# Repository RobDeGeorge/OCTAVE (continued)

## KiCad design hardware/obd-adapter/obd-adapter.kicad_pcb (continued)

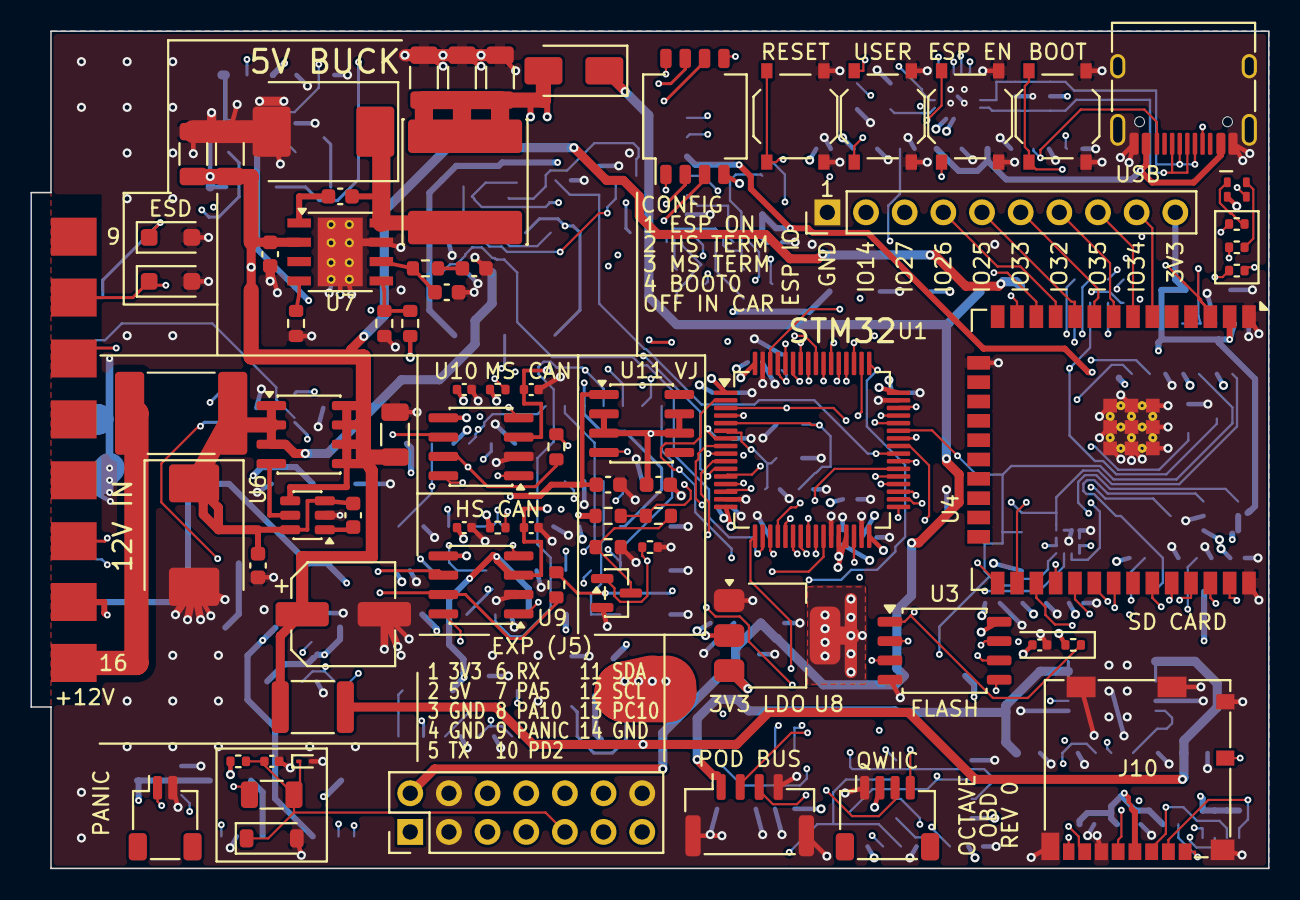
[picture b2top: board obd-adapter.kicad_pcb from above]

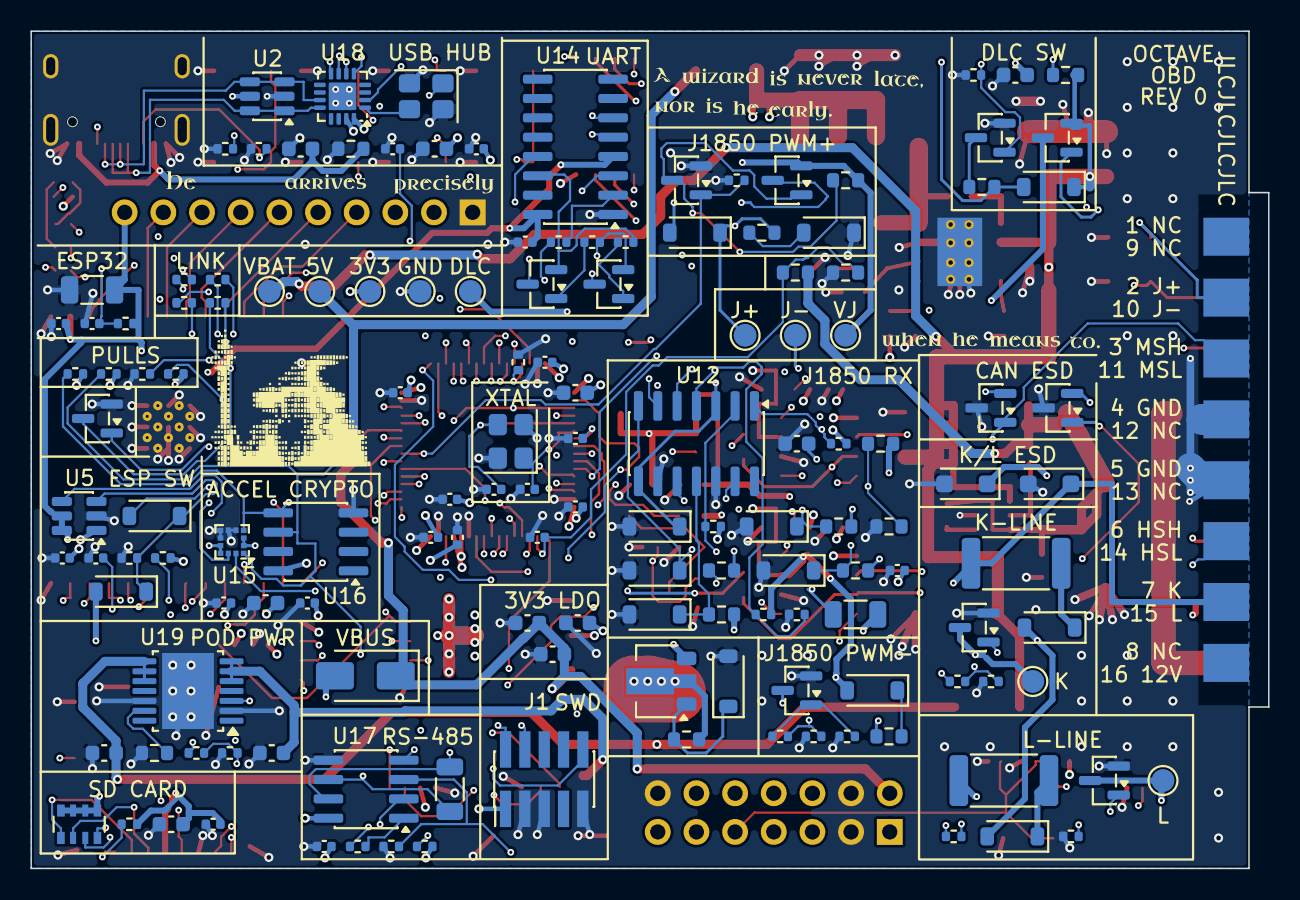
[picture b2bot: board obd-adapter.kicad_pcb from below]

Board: 6 copper layers, 81.3 x 55.0 mm, 218 parts (144 on the bottom side), 151 nets.

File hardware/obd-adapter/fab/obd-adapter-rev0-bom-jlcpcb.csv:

Comment,Designator,Footprint,LCSC
100n,"C1,C2,C3,C4,C6,C9,C13,C15,C35,C36,C37,C38,C39,C45,C46,C48,C49,C51,C54,C57,C58",C_0402_1005Metric,C307331
4.7u,C5,C_0603_1608Metric,C19666
1u,"C7,C16,C18,C56",C_0402_1005Metric,C52923
10p,"C10,C11",C_0402_1005Metric,C32949
10u,"C12,C32,C33,C34,C47,C50,C55",C_0603_1608Metric,C96446
22u,C14,C_1206_3216Metric,C12891
1n,C17,C_0402_1005Metric,C1523
100n,"C19,C20,C23,C26,C41,C43",C_0603_1608Metric,C14663
10u,C21,C_1206_3216Metric,C13585
47u 50V,C22,CP_Elec_6.3x7.7,C2887275
2.2u,"C24,C25",C_1206_3216Metric,C50254
6.8n,C27,C_0603_1608Metric,C1631
47p,C28,C_0603_1608Metric,C1671
47u,"C29,C30,C31",C_1206_3216Metric,C96123
1u,"C40,C42,C52,C53",C_0603_1608Metric,C15849
RGB,D1,LED_RGB_1615,C965840
5.0SMDJ33CA,D4,D_SMC,C2913642
B560C,D5,D_SMC,C85100
SS34,"D6,D7",D_SMA,C8678
SZNUP2105L,"D8,D9",SOT-23,C233494
BZT52C12,D10,D_SOD-123,C19077410
B5819W,"D11,D12,D13",D_SOD-123,C8598
BZT52C33,D14,D_SOD-123,C173417
1N4148W,"D15,D16,D17,D18,D21,D23,D26,D27",D_SOD-123,C81598
SMF24A,"D19,D20,D22,D24",D_SOD-123F,C19077514
ESD9B3.3ST5G,D28,D_SOD-923,C96512
BZT52C5V1,D30,D_SOD-123,C19077401
BZT52C30,D31,D_SOD-123,C19077418
2A 60V,F1,Fuse_2920_7451Metric,C49326266
0.5A 60V,F2,Fuse_1812_4532Metric,C19078719
SWD,J1,PinHeader_2x05_P1.27mm_Vertical_SMD,C41376037
USB-C,J2,USB_C_Receptacle_HRO_TYPE-C-31-M-12,C165948
Qwiic,J4,JST_SH_SM04B-SRSS-TB_1x04-1MP_P1.00mm_Horizontal,C160404
PANIC,J9,JST_SH_SM02B-SRSS-TB_1x02-1MP_P1.00mm_Horizontal,C160402
microSD,J10,microSD_HC_Molex_104031-0811,C585350
POD BUS,J11,JST_GH_SM04B-GHS-TB_1x04-1MP_P1.25mm_Horizontal,C189895
8.2u,L1,L_Changjiang_FNR8065S,C96978
AO4264E,Q1,SOIC-8_3.9x4.9mm_P1.27mm,C334232
SI2309CDS,Q2,SOT-23,C10493
AO3401A,Q6,SOT-23,C15127
MMBT3904,"Q7,Q8,Q9,Q10,Q11",SOT-23,C20526
2N7002,"Q3,Q4,Q5,Q14",SOT-23,C8545
BCX56-16,Q15,SOT-89-3,C100026
10k,"R1,R8,R9,R18,R35,R36,R47,R50,R64,R65,R68",R_0402_1005Metric,C25744
1k,"R3,R11,R12,R13,R14,R39,R63,R70,R76",R_0402_1005Metric,C11702
330,"R4,R5",R_0402_1005Metric,C25104
5.1k,"R6,R7",R_0402_1005Metric,C25905
100k,"R15,R31,R40,R53,R56,R67,R73,R74,R75,R78",R_0402_1005Metric,C25741
4.7k,"R16,R17,R25,R27,R79",R_0402_1005Metric,C25900
160k,R19,R_0603_1608Metric,C22813
68k,R20,R_0603_1608Metric,C23231
12k,R21,R_0603_1608Metric,C22790
13k,R22,R_0603_1608Metric,C22797
100k 0.1%,R23,R_0603_1608Metric,C122538
10k 0.1%,R24,R_0603_1608Metric,C95204
120,"R26,R28",R_0603_1608Metric,C22787
47k,R29,R_0603_1608Metric,C25819
10k,"R30,R38,R42,R44,R48,R49,R57,R58,R59",R_0603_1608Metric,C25804
240,R32,R_0603_1608Metric,C23350
680,R33,R_0603_1608Metric,C23228
470,R34,R_0603_1608Metric,C23179
1.5k,R37,R_0603_1608Metric,C22843
2.2k,R41,R_0402_1005Metric,C25879
1k,R43,R_1206_3216Metric,C4410
18k,R45,R_0402_1005Metric,C25762
47k,R46,R_0402_1005Metric,C25792
510 2W,"R51,R54",R_2512_6332Metric,C5843118
470,"R52,R55",R_0402_1005Metric,C25117
2k,R66,R_1206_3216Metric,C17944
3k,R72,R_0603_1608Metric,C4211
120,R77,R_1206_3216Metric,C17909
1k,"R69,R80",R_0603_1608Metric,C21190
4x10k,RN1,R_Array_Convex_4x0603,C29718
ESP_BOOT / ESP_RST / RESET / USER,"SW1,SW3,SW4,SW5",SW_Push_1P1T_XKB_TS-1187A,C318884
CONFIG,SW6,SW_DIP_SPSTx04_Slide_KingTek_DSHP04TS_W7.62mm_P1.27mm,C40736
STM32G474RET6,U1,LQFP-64_10x10mm_P0.5mm,C521608
USBLC6-2SC6,U2,SOT-23-6,C2687116
W25Q128JVSIQ,U3,SOIC-8_5.3x5.3mm_P1.27mm,C97521
ESP32-WROOM-32E-N8,U4,ESP32-WROOM-32E,C701342
TPS22918,U5,SOT-23-6,C131941
LM74700QDBVRQ1,U6,SOT-23-6,C2941042
TPS54360BDDAR,U7,TI_SO-PowerPAD-8_ThermalVias,C524806
AP2114H-3.3,U8,SOT-223-3_TabPin2,C150716
TCAN1044VDRQ1,"U9,U10",SOIC-8_3.9x4.9mm_P1.27mm,C1852061
LM317LIDR,U11,SOIC-8_3.9x4.9mm_P1.27mm,C183332
LM2901BIDR,U12,SOIC-14_3.9x8.7mm_P1.27mm,C22427890
CH340C,U14,SOIC-16_3.9x9.9mm_P1.27mm,C84681
LIS2DH12TR,U15,LGA-12_2x2mm_P0.5mm,C110926
ATECC608B-SSHDA-T,U16,SOIC-8_3.9x4.9mm_P1.27mm,C1518769
THVD2450DR,U17,SOIC-8_3.9x4.9mm_P1.27mm,C2672621
CH334P,U18,WCH_QFN-16-1EP_3x3mm_P0.5mm_EP1.8x1.8mm,C5373042
TPS27S100APWPR,U19,Texas_HTSSOP-14-1EP_4.4x5mm_P0.65mm_EP3.4x5mm_Mask2.94x3.34mm,C2879389
16MHz,Y1,Crystal_SMD_3225-4Pin_3.2x2.5mm,C13738
12MHz,Y2,Crystal_SMD_3225-4Pin_3.2x2.5mm,C9002

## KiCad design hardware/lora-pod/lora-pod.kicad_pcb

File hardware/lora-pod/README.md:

# OCTAVE LoRa pod, Rev 0

The dash-top half of the LoRa car finder (`TODO/lora-car-finder.md`, step 4): the parked car's position, beaconed over LoRa, with Bluetooth for a phone. It is the first pod on the OCTAVE pod bus (`../pod-bus/README.md`): battery voltage and RS-485 on four wires, in on one connector and out on the other. Rev 0 is a bring-up board: room to probe, unfitted headers for the things still undecided.

**Status (2026-11-23):** schematic generated, ERC clean (0 errors, 0 warnings). Board placed and **routed** (again the same day, after the cable changed from a plain UART to the pod bus): 0 unconnected pads, schematic and board agree, 2 DRC warnings, both cosmetic (the USB-C socket's outline runs off the board edge). The route is the autorouter's and has passed the rule check, not a person's eye. No fab files, no firmware. Not reviewed by a human. Nothing has been measured.

## What is on it

95 x 46 mm, 4 layers, every part on top (54 parts).

| Block | Part | Notes |
|---|---|---|
| MCU + radios | RAK4630-9-SM-I (nRF52840 + SX1262) | LoRa 902-928 MHz and Bluetooth LE. Both antennas plug into IPEX sockets on the module: no RF trace on this board. Europe: RAK4630-8-SM-I, same footprint. |
| GPS | Quectel L80-R (order code L80RE-M37) | GPS only, 15 mm patch antenna on top. Its supply is switched (TPS22918); V_BCKP is held by a 0.1 F supercap (hand-fit). |
| IMU | ASM330LHH | I2C 0x6A. "Moved while parked". |
| Supply | 0.5 A / 30 V polyfuse, SMBJ24A, B5819W, TPS7B8233 | 5 to 16 V in. See "Pod bus and supply". |
| Pod bus | two JST GH (J1, J7), THVD2450 RS-485 transceiver, 120 Ω behind the `END` switch (SW3) | |
| USB-C | the module's own USB | Firmware update, console, 5 V on the bench. |
| Bring-up | SWD, Qwiic, RESET, PAIR, two LEDs, `BENCH` and `RANGE` headers (not fitted) | |

## Pod bus and supply

J1 and J7 (JST GH) carry the same four nets, pin for pin: 1 `VIN`, 2 RS-485 `A`, 3 RS-485 `B`, 4 GND. Either is the way in; the other goes on to the next pod.

- **On the chain:** `VIN` is the car's battery, switched and fused by the OBD adapter. The chain's current passes from J1 to J7 on the board, ahead of this pod's own fuse.
- **Standalone:** `VIN` is the battery (OBD pin 16, always on) through a plain power lead; pins 2 / 3 open.
- **Last pod of the chain:** both poles of SW3 (`END`) on. That puts 120 Ω across A / B.

F1 and D1 take a reversed lead, a 24 V jump start and a load dump (D1 clamps at 38.9 V, under U1's 40 V). `VBAT_SENSE` (P0.31) reads `VIN` x 0.180: the battery's voltage, and whether the alternator is charging, so the pod knows "parked" without the adapter. The divider draws 10 µA at 12.6 V.

U7 (THVD2450) survives ±70 V on A / B, so a cable pinched against `VIN` does not kill it, and it has its own ESD protection and idle-bus failsafe: there is no TVS and no bias resistor on the bus. Its driver and receiver enables are separate pins. With both idle (the state at reset: 100k each) it is shut down, under 1 µA; listening costs 1.8 mA, so the firmware must shut it down while parked.

At 14 V the regulator burns about 0.4 W with the GPS on (an estimate: 40 mA). It is the first thing to measure on a hot dash; a small switching regulator is the fix.

## Pin plan (nRF52840)

| Signal | Pin | | Signal | Pin |
|---|---|---|---|---|
| I2C SDA / SCL | P0.13 / P0.14 | | PAIR button | P1.01 |
| GPS UART (from / to GPS) | P0.15 / P0.16 | | GNSS_EN | P1.02 |
| Pod bus UART RX / TX | P0.19 / P0.20 | | LED green / red | P1.03 / P1.04 |
| SPI SCK / MOSI / MISO / NSS (`RANGE`) | P0.17 / P0.21 / P0.24 / P0.25 | | GPS 1PPS | P0.03 |
| RANGE_IRQ | P0.29 | | IMU INT1 / INT2 | P0.02 / P0.28 |
| RS-485 driver enable / receiver enable (low) | P0.30 / P0.26 | | VBAT_SENSE | P0.31 (AIN7) |
| Spare (headers) | P0.04, P0.05 | | | |

Fast signals are on the pins Nordic allows above 10 kHz; the slow ones are on the low-frequency pins near the radio.

## Files

| File | |
|---|---|
| `gen/lora_pod.py` | **The design:** every part, its LCSC number, its pin-to-net map. Edit this, not the KiCad files. |
| `gen/pod_parts.py` | LCSC numbers, checked against JLCPCB on 2026-11-23. |
| `gen/pod_layout.py` | Placement: every part's position. |
| `gen/pod_libdefs.py` | Project symbols (RAK4630, TPS7B82, ASM330LHH, the RS-485 transceiver) and the RAK4630 footprint. |
| `gen/build.py` | `python3 build.py sch`, then `pcb`, `route`, `view` (system `python3`, KiCad 10, Freerouting 2.5 as for the adapter). Uses the OBD adapter's generator modules (`../obd-adapter/gen`). |
| `gen/routing.json` | The routing, frozen: `route` replays it and refuses if a part moved. `POD_REROUTE=1` routes afresh (about 3 minutes), then run `pcb` and `route` once more: the first pass takes the autorouter's stub vias out of the file. The autorouter does not give the same result twice; one run in three so far left a pad of the IMU open and had to be repeated. |
| `gen/review.py` | The annotated top view in `view/`. |
| `lib/3dmodels/` | LCSC models of the two modules, fetched with easyeda2kicad. |

## Before ordering

- Look at the copper in KiCad: DRC does not judge quality. GND is In1, 3V3 is In2, signals on the outer layers; supply nets are 0.4 to 0.5 mm.
- Fab outputs: `build.py` has no `fab` step yet (the adapter's is the model), and the JLCPCB rotation corrections for the new parts are not worked out.
- **RAK4630-9-SM-I had 44 in stock** on 2026-11-23. Recheck first.
- The RAK4630 footprint's land positions come from the LCSC footprint and its numbering from the datasheet's figure 1: check it against a module or the datasheet's figure 5 before ordering.
- Thermal: the modules and the GPS are rated to 85 °C; a dash top in the sun passes 80 °C. Find a supercap rated for it.
- Firmware obligations so far: drive `GNSS_RXD_M` low while `GNSS_EN` is low; `GNSS_EN` is off at reset (100k); shut the RS-485 transceiver down while parked.
- The other end of the pod bus is J11 on the OBD adapter's bottom edge (`../obd-adapter/README.md`, "Pod bus"). That board was reworked into a compact two-sided one on 2026-11-24: see its README for where it stands.
- R3, R4, D3 and D4 do not exist (they were the plain-UART cable's parts): the numbering has those gaps on purpose.
- US 915 MHz rules (hopping or a 500 kHz channel) and whether the module's FCC grant covers the antenna used: not verified.

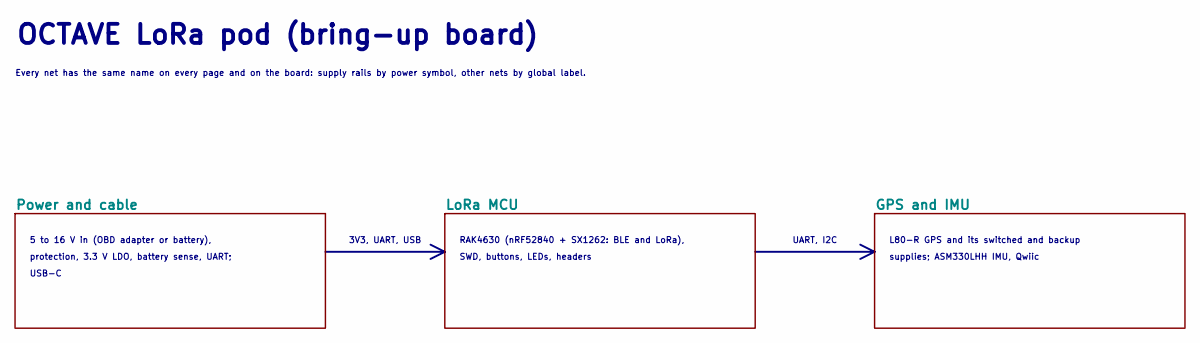
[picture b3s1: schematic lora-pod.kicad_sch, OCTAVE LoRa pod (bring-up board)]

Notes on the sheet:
5 to 16 V in (OBD adapter or battery),
protection, 3.3 V LDO, battery sense, UART;
USB-C
RAK4630 (nRF52840 + SX1262: BLE and LoRa),
SWD, buttons, LEDs, headers
L80-R GPS and its switched and backup
supplies; ASM330LHH IMU, Qwiic
3V3, UART, USB
UART, I2C
OCTAVE LoRa pod (bring-up board)
Every net has the same name on every page and on the board: supply rails by power symbol, other nets by global label.

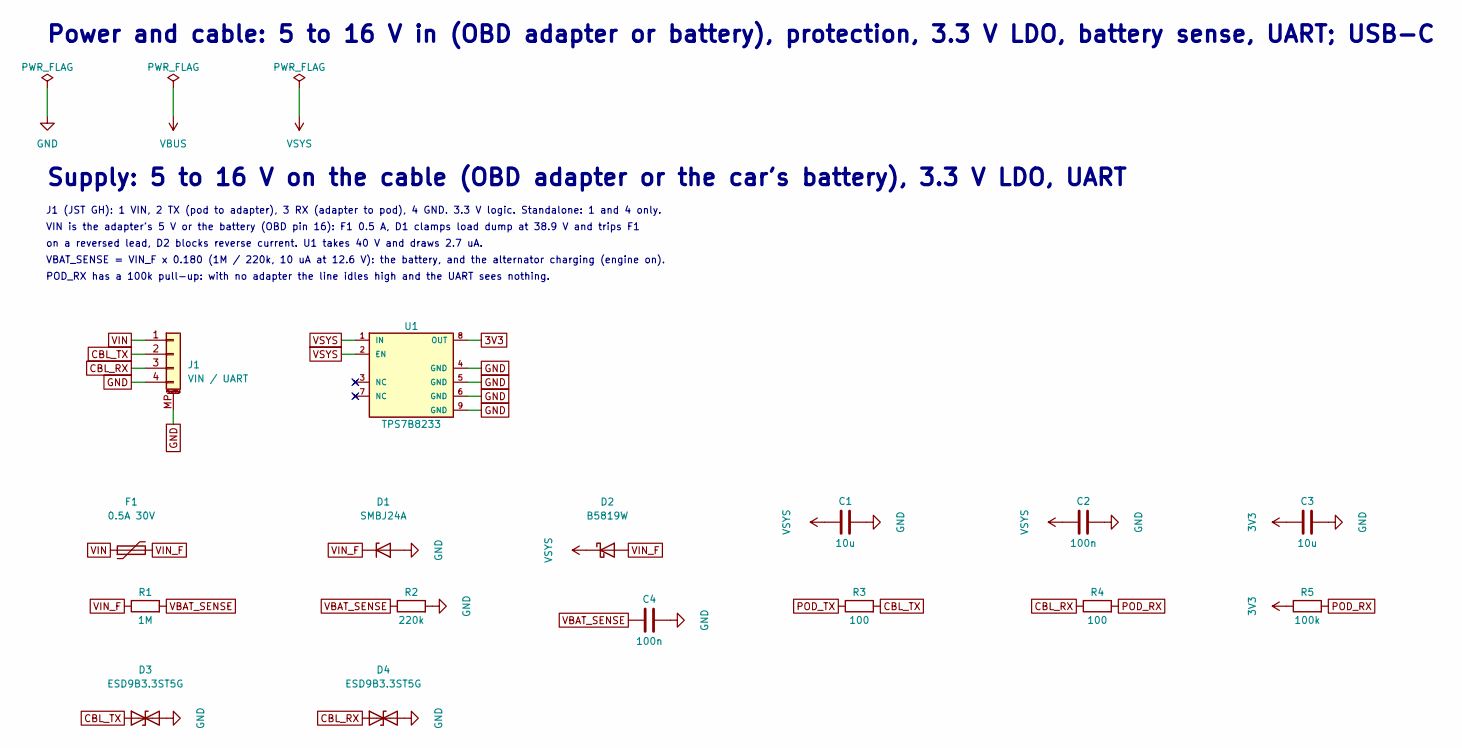
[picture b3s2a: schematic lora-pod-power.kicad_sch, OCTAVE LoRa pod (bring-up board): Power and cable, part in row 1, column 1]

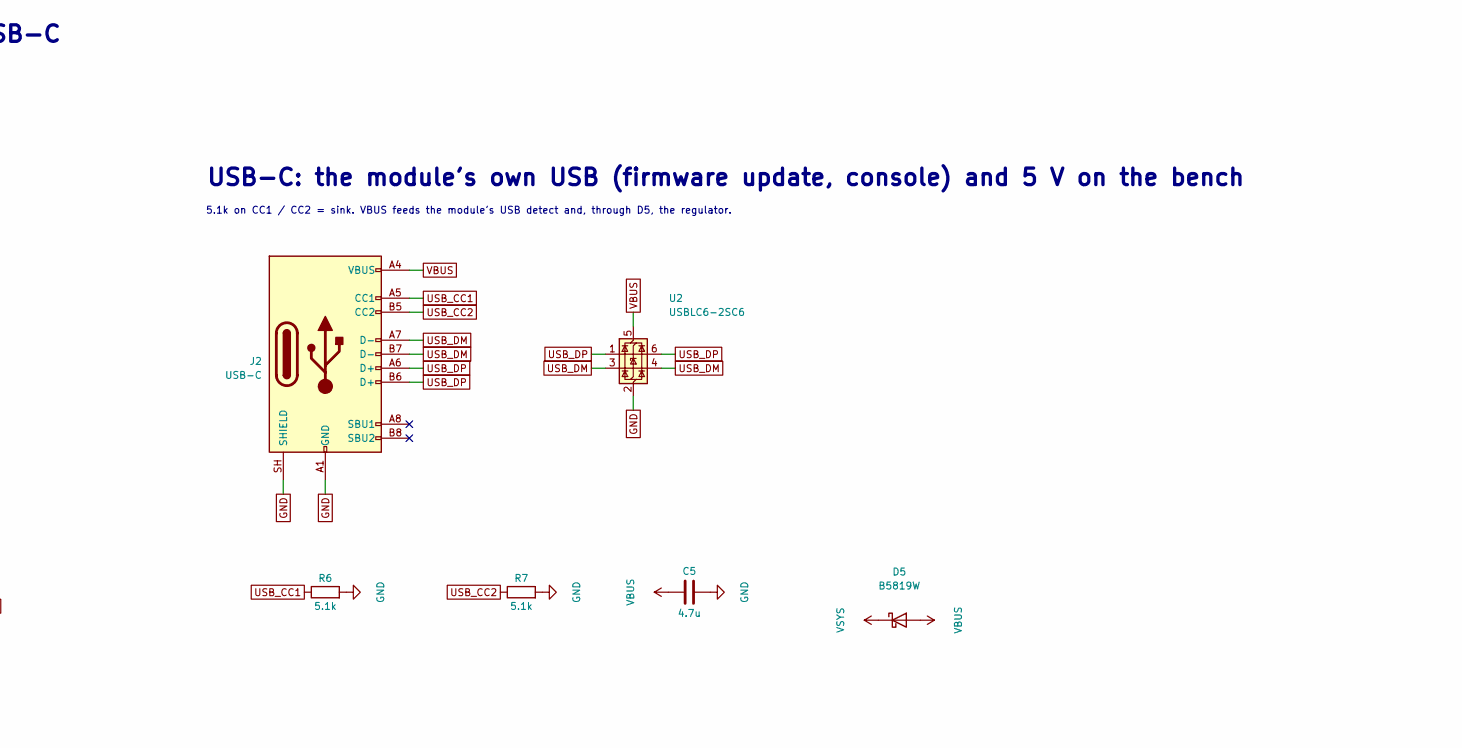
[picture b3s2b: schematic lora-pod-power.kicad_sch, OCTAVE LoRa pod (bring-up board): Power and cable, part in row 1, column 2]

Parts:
C1: 10u; C_1206_3216Metric; LCSC C13585
C2, C4: 100n; C_0603_1608Metric; LCSC C14663
C3: 10u; C_0603_1608Metric; LCSC C96446
C5: 4.7u; C_0603_1608Metric; LCSC C19666
D1: SMBJ24A; D_SMB; LCSC C123819
D2, D5: B5819W; D_SOD-123; LCSC C8598
D3, D4: ESD9B3.3ST5G; D_SOD-923; LCSC C96512
F1: 0.5A 30V; Fuse_1206_3216Metric; LCSC C7542947
J1: VIN / UART; JST_GH_SM04B-GHS-TB_1x04-1MP_P1.25mm_Horizontal; LCSC C189895
J2: USB-C; USB_C_Receptacle_HRO_TYPE-C-31-M-12; LCSC C165948
R1: 1M; R_0603_1608Metric; LCSC C22935
R2: 220k; R_0603_1608Metric; LCSC C22961
R3, R4: 100; R_0603_1608Metric; LCSC C22775
R5: 100k; R_0603_1608Metric; LCSC C25803
R6, R7: 5.1k; R_0603_1608Metric; LCSC C23186
U1: TPS7B8233; HVSSOP-8-1EP_3x3mm_P0.65mm_EP1.57x1.89mm; LCSC C5220182
U2: USBLC6-2SC6; SOT-23-6; LCSC C2687116

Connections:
3V3: C3.1, R5.1, U1.8 (OUT); also elsewhere on the board
CBL_RX: D4.1 (A1), J1.3, R4.1; also elsewhere on the board
CBL_TX: D3.1 (A1), J1.2, R3.2; also elsewhere on the board
GND: C1.2, C2.2, C3.2, C4.2, C5.2, D1.2 (A), D3.2 (A2), D4.2 (A2), J1.4, J1.MP (MountPin), J2.A1 (GND), J2.A12 (GND), J2.B1 (GND), J2.B12 (GND), J2.SH (SHIELD), R2.2, R6.2, R7.2, U1.4 (GND), U1.5 (GND), U1.6 (GND), U1.9 (GND), U2.2 (GND); also elsewhere on the board
POD_RX: R4.2, R5.2; also elsewhere on the board
POD_TX: R3.1; also elsewhere on the board
USB_CC1: J2.A5 (CC1), R6.1
USB_CC2: J2.B5 (CC2), R7.1
USB_DM: J2.A7 (D-), J2.B7 (D-), U2.3 (I/O2), U2.4 (I/O2); also elsewhere on the board
USB_DP: J2.A6 (D+), J2.B6 (D+), U2.1 (I/O1), U2.6 (I/O1); also elsewhere on the board
VBAT_SENSE: C4.1, R1.2, R2.1; also elsewhere on the board
VBUS: C5.1, D5.2 (A), J2.A4 (VBUS), J2.A9 (VBUS), J2.B4 (VBUS), J2.B9 (VBUS), U2.5 (VBUS); also elsewhere on the board
VIN: F1.1, J1.1; also elsewhere on the board
VIN_F: D1.1 (K), D2.2 (A), F1.2, R1.1
VSYS: C1.1, C2.1, D2.1 (K), D5.1 (K), U1.1 (IN), U1.2 (EN)

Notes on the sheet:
Power and cable: 5 to 16 V in (OBD adapter or battery), protection, 3.3 V LDO, battery sense, UART; USB-C
Supply: 5 to 16 V on the cable (OBD adapter or the car's battery), 3.3 V LDO, UART
J1 (JST GH): 1 VIN, 2 TX (pod to adapter), 3 RX (adapter to pod), 4 GND. 3.3 V logic. Standalone: 1 and 4 only.
VIN is the adapter's 5 V or the battery (OBD pin 16): F1 0.5 A, D1 clamps load dump at 38.9 V and trips F1
on a reversed lead, D2 blocks reverse current. U1 takes 40 V and draws 2.7 uA.
VBAT_SENSE = VIN_F x 0.180 (1M / 220k, 10 uA at 12.6 V): the battery, and the alternator charging (engine on).
POD_RX has a 100k pull-up: with no adapter the line idles high and the UART sees nothing.
USB-C: the module's own USB (firmware update, console) and 5 V on the bench
5.1k on CC1 / CC2 = sink. VBUS feeds the module's USB detect and, through D5, the regulator.

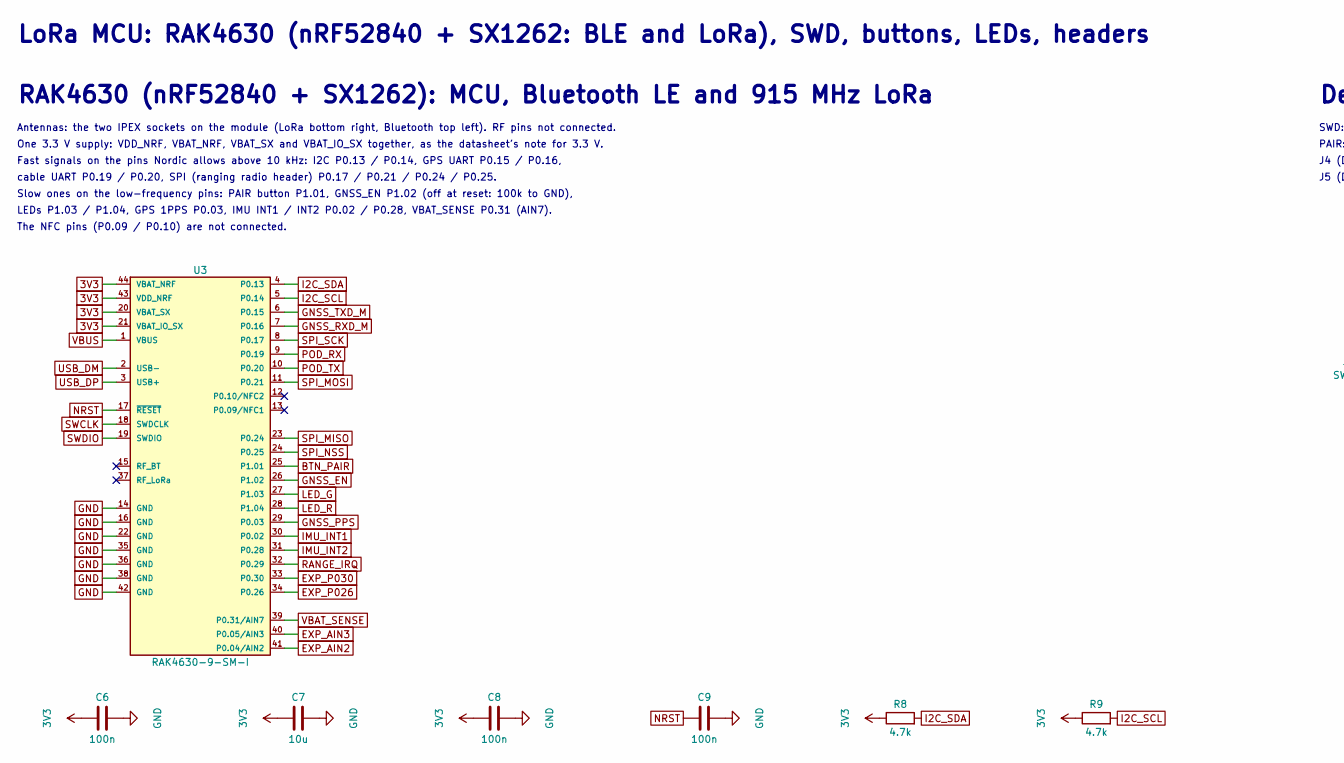
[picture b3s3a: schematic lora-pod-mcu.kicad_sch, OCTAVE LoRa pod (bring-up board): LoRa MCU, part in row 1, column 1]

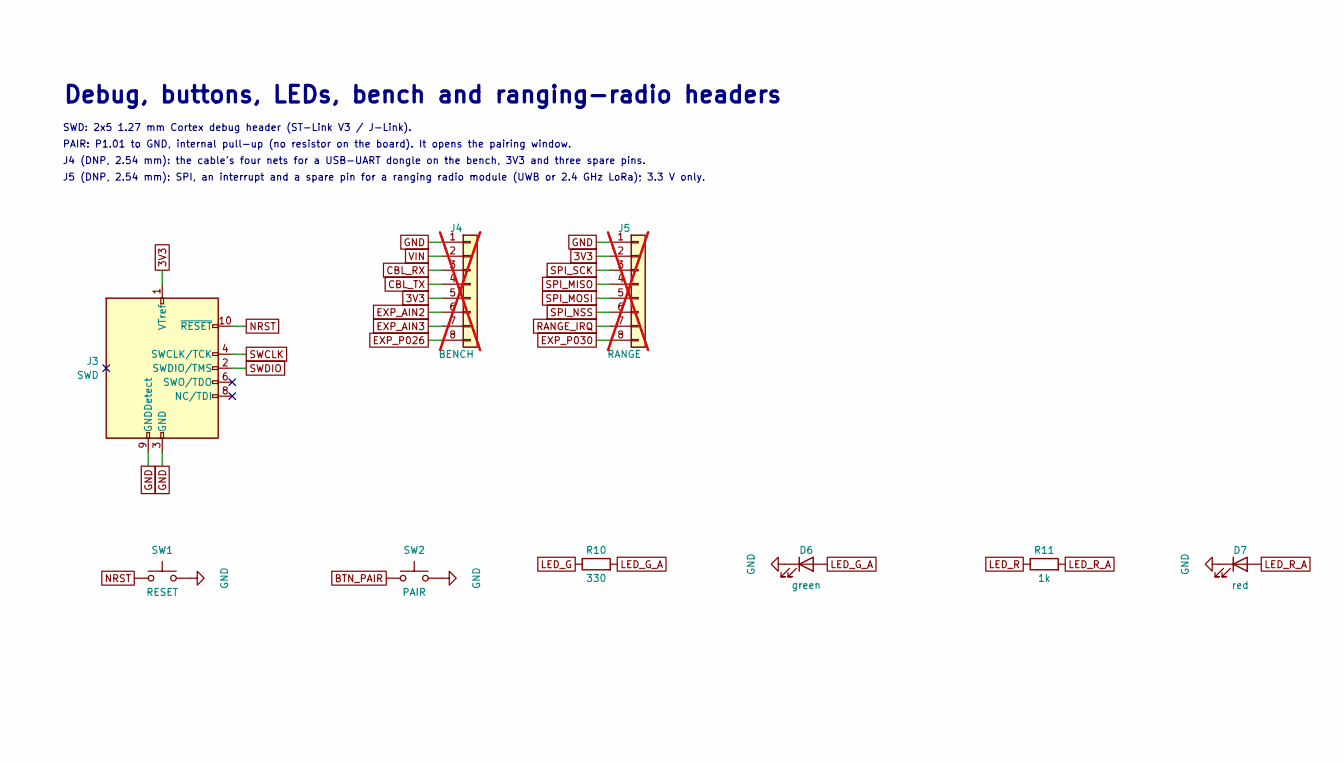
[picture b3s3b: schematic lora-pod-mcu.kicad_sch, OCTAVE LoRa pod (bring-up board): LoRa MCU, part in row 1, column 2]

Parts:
C6, C8, C9: 100n; C_0603_1608Metric; LCSC C14663
C7: 10u; C_0603_1608Metric; LCSC C96446
D6: green; LED_0603_1608Metric; LCSC C12624
D7: red; LED_0603_1608Metric; LCSC C2286
J3: SWD; PinHeader_2x05_P1.27mm_Vertical_SMD; LCSC C41376037
J4: BENCH; PinHeader_1x08_P2.54mm_Vertical; not fitted
J5: RANGE; PinHeader_1x08_P2.54mm_Vertical; not fitted
R8, R9: 4.7k; R_0603_1608Metric; LCSC C23162
R10: 330; R_0603_1608Metric; LCSC C23138
R11: 1k; R_0603_1608Metric; LCSC C21190
SW1: RESET; SW_Push_1P1T_XKB_TS-1187A; LCSC C318884
SW2: PAIR; SW_Push_1P1T_XKB_TS-1187A; LCSC C318884
U3: RAK4630-9-SM-I; RAK4630; LCSC C33033533

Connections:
3V3: C6.1, C7.1, C8.1, J3.1 (VTref), J4.5, J5.2, R8.1, R9.1, U3.20 (VBAT_SX), U3.21 (VBAT_IO_SX), U3.43 (VDD_NRF), U3.44 (VBAT_NRF); also elsewhere on the board
BTN_PAIR: SW2.1, U3.25 (P1.01)
CBL_RX: J4.3; also elsewhere on the board
CBL_TX: J4.4; also elsewhere on the board
EXP_AIN2: J4.6, U3.41 (P0.04/AIN2)
EXP_AIN3: J4.7, U3.40 (P0.05/AIN3)
EXP_P026: J4.8, U3.34 (P0.26)
EXP_P030: J5.8, U3.33 (P0.30)
GND: C6.2, C7.2, C8.2, C9.2, D6.1 (K), D7.1 (K), J3.3 (GND), J3.5 (GND), J3.9 (GNDDetect), J4.1, J5.1, SW1.2, SW2.2, U3.14 (GND), U3.16 (GND), U3.22 (GND), U3.35 (GND), U3.36 (GND), U3.38 (GND), U3.42 (GND); also elsewhere on the board
GNSS_EN: U3.26 (P1.02); also elsewhere on the board
GNSS_PPS: U3.29 (P0.03); also elsewhere on the board
GNSS_RXD_M: U3.7 (P0.16); also elsewhere on the board
GNSS_TXD_M: U3.6 (P0.15); also elsewhere on the board
I2C_SCL: R9.2, U3.5 (P0.14); also elsewhere on the board
I2C_SDA: R8.2, U3.4 (P0.13); also elsewhere on the board
IMU_INT1: U3.30 (P0.02); also elsewhere on the board
IMU_INT2: U3.31 (P0.28); also elsewhere on the board
LED_G: R10.1, U3.27 (P1.03)
LED_G_A: D6.2 (A), R10.2
LED_R: R11.1, U3.28 (P1.04)
LED_R_A: D7.2 (A), R11.2
NRST: C9.1, J3.10 (~RESET), SW1.1, U3.17 (~RESET)
POD_RX: U3.9 (P0.19); also elsewhere on the board
POD_TX: U3.10 (P0.20); also elsewhere on the board
RANGE_IRQ: J5.7, U3.32 (P0.29)
SPI_MISO: J5.4, U3.23 (P0.24)
SPI_MOSI: J5.5, U3.11 (P0.21)
SPI_NSS: J5.6, U3.24 (P0.25)
SPI_SCK: J5.3, U3.8 (P0.17)
SWCLK: J3.4 (SWCLK/TCK), U3.18 (SWDCLK)
SWDIO: J3.2 (SWDIO/TMS), U3.19 (SWDIO)
USB_DM: U3.2 (USB-); also elsewhere on the board
USB_DP: U3.3 (USB+); also elsewhere on the board
VBAT_SENSE: U3.39 (P0.31/AIN7); also elsewhere on the board
VBUS: U3.1 (VBUS); also elsewhere on the board
VIN: J4.2; also elsewhere on the board

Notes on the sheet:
LoRa MCU: RAK4630 (nRF52840 + SX1262: BLE and LoRa), SWD, buttons, LEDs, headers
RAK4630 (nRF52840 + SX1262): MCU, Bluetooth LE and 915 MHz LoRa
Antennas: the two IPEX sockets on the module (LoRa bottom right, Bluetooth top left). RF pins not connected.
One 3.3 V supply: VDD_NRF, VBAT_NRF, VBAT_SX and VBAT_IO_SX together, as the datasheet's note for 3.3 V.
Fast signals on the pins Nordic allows above 10 kHz: I2C P0.13 / P0.14, GPS UART P0.15 / P0.16,
cable UART P0.19 / P0.20, SPI (ranging radio header) P0.17 / P0.21 / P0.24 / P0.25.
Slow ones on the low-frequency pins: PAIR button P1.01, GNSS_EN P1.02 (off at reset: 100k to GND),
LEDs P1.03 / P1.04, GPS 1PPS P0.03, IMU INT1 / INT2 P0.02 / P0.28, VBAT_SENSE P0.31 (AIN7).
The NFC pins (P0.09 / P0.10) are not connected.
Debug, buttons, LEDs, bench and ranging-radio headers
SWD: 2x5 1.27 mm Cortex debug header (ST-Link V3 / J-Link).
PAIR: P1.01 to GND, internal pull-up (no resistor on the board). It opens the pairing window.
J4 (DNP, 2.54 mm): the cable's four nets for a USB-UART dongle on the bench, 3V3 and three spare pins.
J5 (DNP, 2.54 mm): SPI, an interrupt and a spare pin for a ranging radio module (UWB or 2.4 GHz LoRa); 3.3 V only.

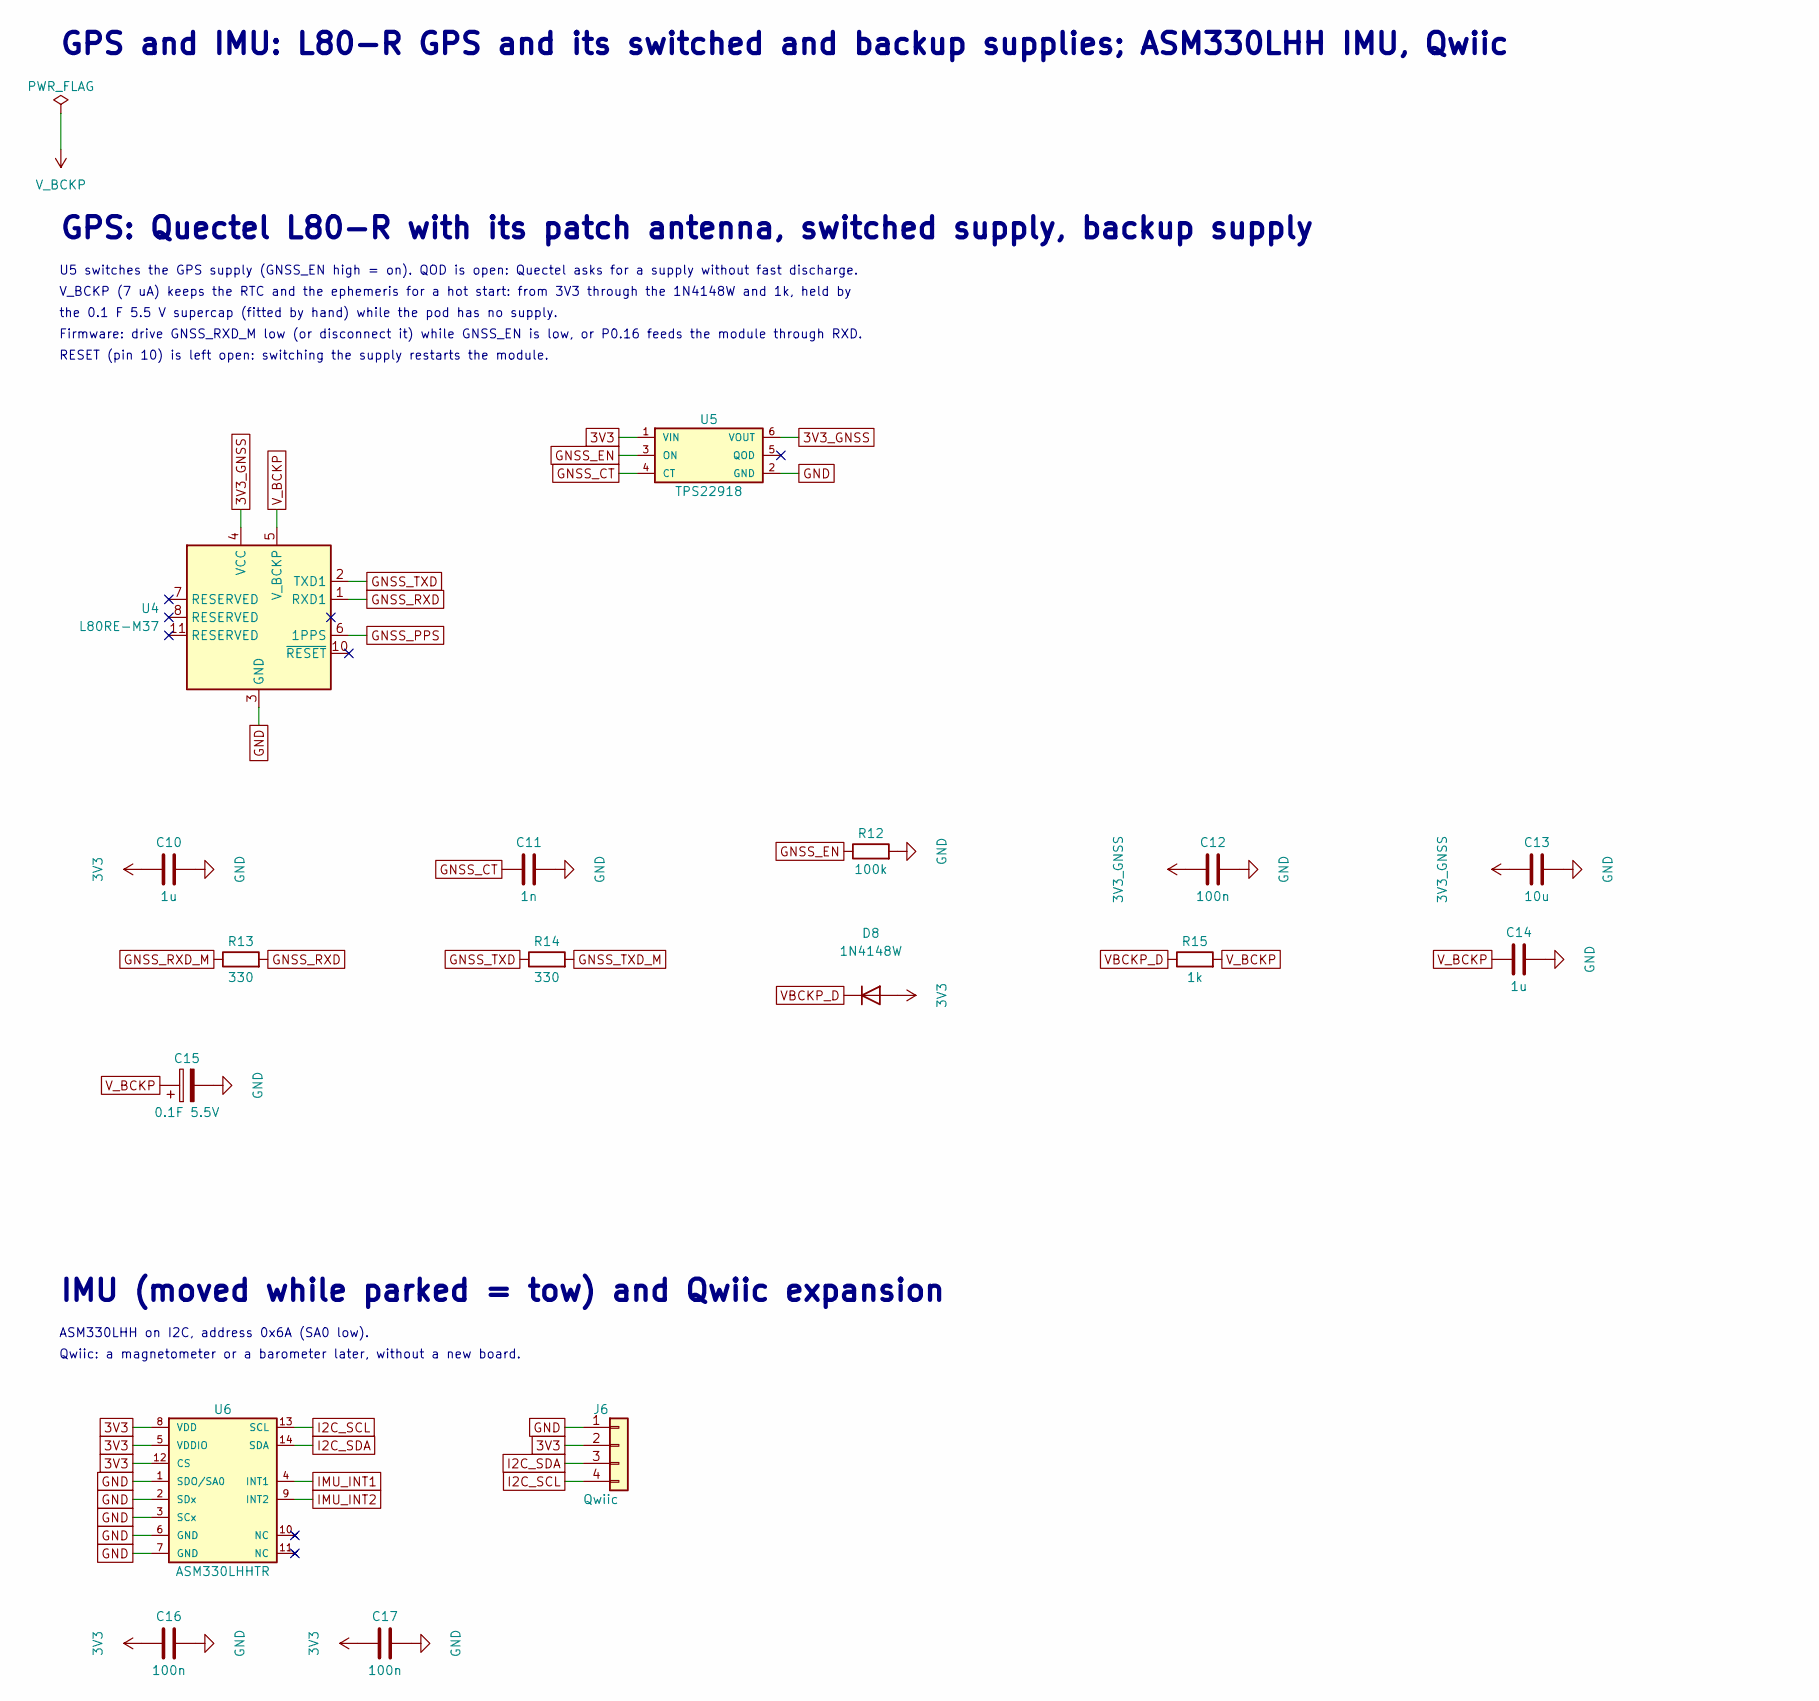
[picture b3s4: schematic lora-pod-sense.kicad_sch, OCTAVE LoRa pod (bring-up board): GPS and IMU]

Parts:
C10, C14: 1u; C_0603_1608Metric; LCSC C15849
C11: 1n; C_0603_1608Metric; LCSC C1588
C12, C16, C17: 100n; C_0603_1608Metric; LCSC C14663
C13: 10u; C_0603_1608Metric; LCSC C96446
C15: 0.1F 5.5V; C_Disc_D11.0mm_W5.0mm_P5.00mm
D8: 1N4148W; D_SOD-123; LCSC C81598
J6: Qwiic; JST_SH_SM04B-SRSS-TB_1x04-1MP_P1.00mm_Horizontal; LCSC C160404
R12: 100k; R_0603_1608Metric; LCSC C25803
R13, R14: 330; R_0603_1608Metric; LCSC C23138
R15: 1k; R_0603_1608Metric; LCSC C21190
U4: L80RE-M37; Quectel_L80-R; LCSC C3029061
U5: TPS22918; SOT-23-6; LCSC C131941
U6: ASM330LHHTR; LGA-14_3x2.5mm_P0.5mm_LayoutBorder3x4y; LCSC C459826

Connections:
3V3: C10.1, C16.1, C17.1, D8.2 (A), J6.2, U5.1 (VIN), U6.5 (VDDIO), U6.8 (VDD), U6.12 (CS); also elsewhere on the board
3V3_GNSS: C12.1, C13.1, U4.4 (VCC), U5.6 (VOUT)
GND: C10.2, C11.2, C12.2, C13.2, C14.2, C15.2, C16.2, C17.2, J6.1, R12.2, U4.3 (GND), U4.12 (GND), U5.2 (GND), U6.1 (SDO/SA0), U6.2 (SDx), U6.3 (SCx), U6.6 (GND), U6.7 (GND); also elsewhere on the board
GNSS_CT: C11.1, U5.4 (CT)
GNSS_EN: R12.1, U5.3 (ON); also elsewhere on the board
GNSS_PPS: U4.6 (1PPS); also elsewhere on the board
GNSS_RXD: R13.2, U4.1 (RXD1)
GNSS_RXD_M: R13.1; also elsewhere on the board
GNSS_TXD: R14.1, U4.2 (TXD1)
GNSS_TXD_M: R14.2; also elsewhere on the board
I2C_SCL: J6.4, U6.13 (SCL); also elsewhere on the board
I2C_SDA: J6.3, U6.14 (SDA); also elsewhere on the board
IMU_INT1: U6.4 (INT1); also elsewhere on the board
IMU_INT2: U6.9 (INT2); also elsewhere on the board
VBCKP_D: D8.1 (K), R15.1
V_BCKP: C14.1, C15.1, R15.2, U4.5 (V_BCKP)

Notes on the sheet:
GPS and IMU: L80-R GPS and its switched and backup supplies; ASM330LHH IMU, Qwiic
GPS: Quectel L80-R with its patch antenna, switched supply, backup supply
U5 switches the GPS supply (GNSS_EN high = on). QOD is open: Quectel asks for a supply without fast discharge.
V_BCKP (7 uA) keeps the RTC and the ephemeris for a hot start: from 3V3 through the 1N4148W and 1k, held by
the 0.1 F 5.5 V supercap (fitted by hand) while the pod has no supply.
Firmware: drive GNSS_RXD_M low (or disconnect it) while GNSS_EN is low, or P0.16 feeds the module through RXD.
RESET (pin 10) is left open: switching the supply restarts the module.
IMU (moved while parked = tow) and Qwiic expansion
ASM330LHH on I2C, address 0x6A (SA0 low).
Qwiic: a magnetometer or a barometer later, without a new board.

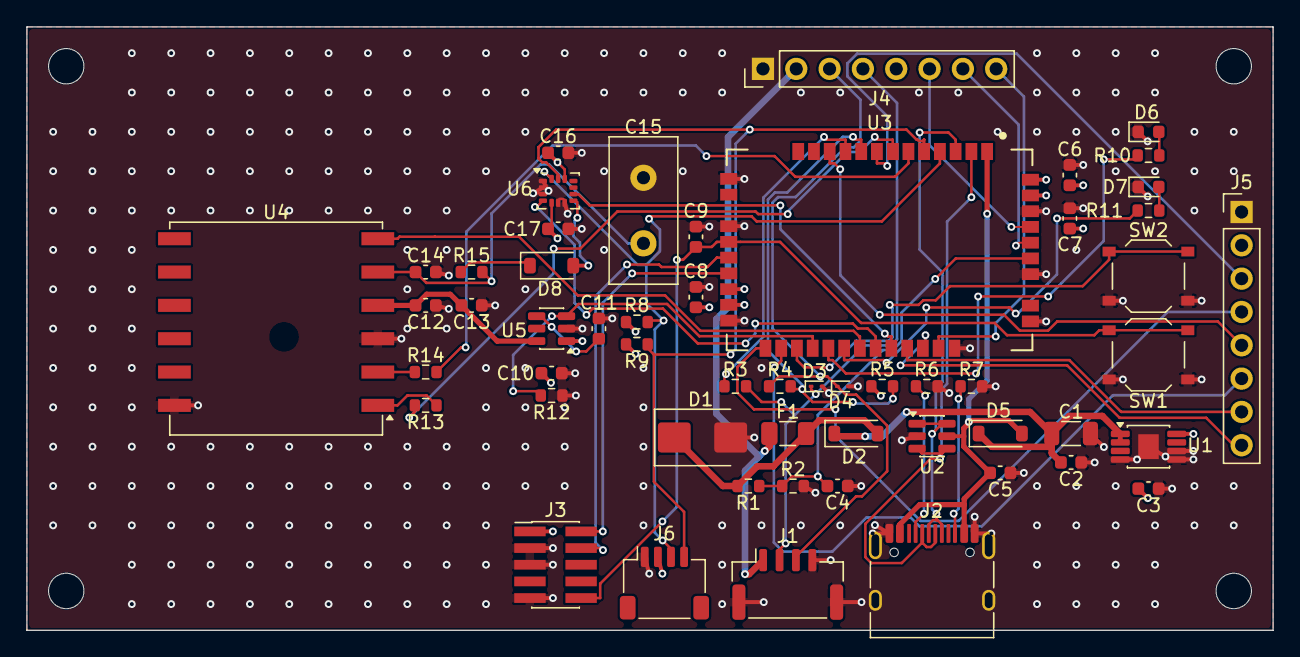
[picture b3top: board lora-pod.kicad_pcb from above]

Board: 4 copper layers, 95.0 x 46.0 mm, 59 parts (0 on the bottom side), 46 nets.

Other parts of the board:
H1, H2, H3, H4: M2.5; MountingHole_2.7mm_M2.5
